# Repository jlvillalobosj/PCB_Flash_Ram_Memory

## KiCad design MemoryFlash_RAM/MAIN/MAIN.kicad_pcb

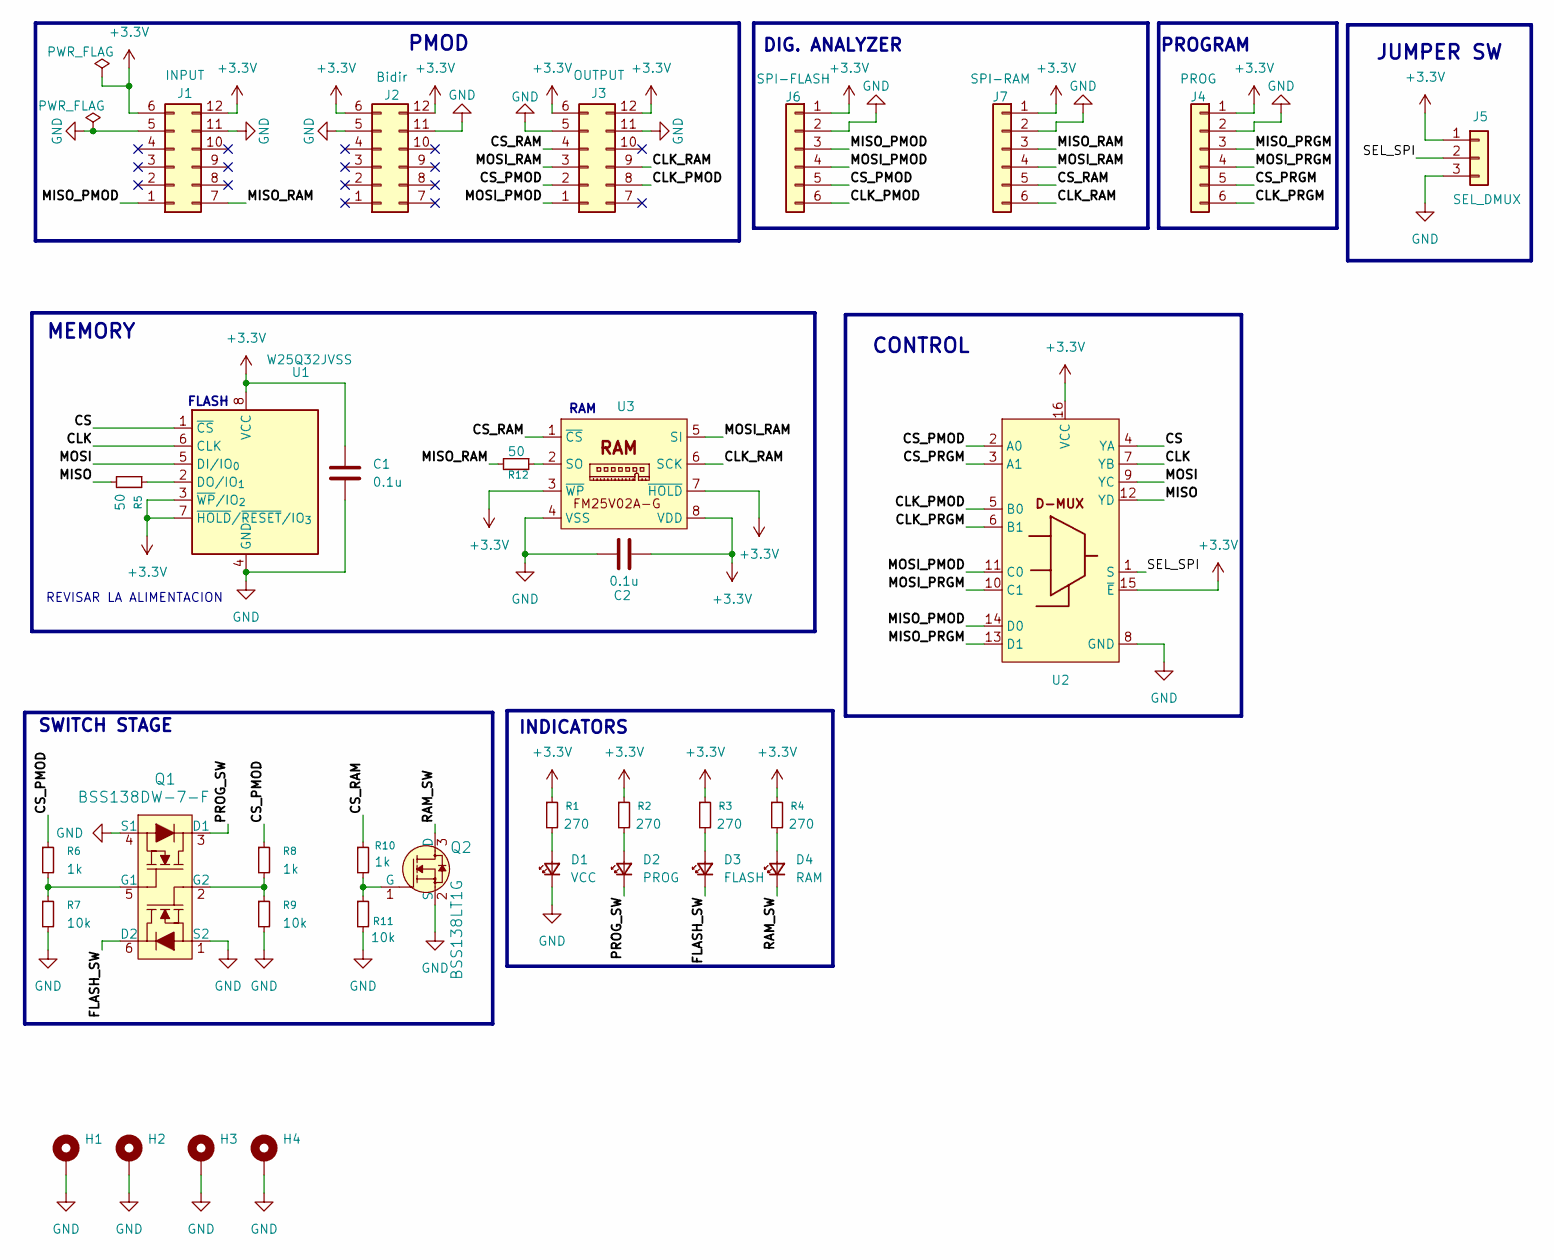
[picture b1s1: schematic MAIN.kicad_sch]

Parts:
C1, C2: 0.1u; C_0805_2012Metric
D1: VCC; LED_2010_5025Metric
D2: PROG; LED_2010_5025Metric
D3: FLASH; LED_2010_5025Metric
D4: RAM; LED_2010_5025Metric
H1, H2, H3, H4: MountingHole_Pad; MountingHole_3.2mm_M3_DIN965_Pad
J1: INPUT; PinHeader_2x06_P2.54mm_Horizontal
J2: Bidir; PinHeader_2x06_P2.54mm_Horizontal
J3: OUTPUT; PinHeader_2x06_P2.54mm_Horizontal
J4: PROG; PinHeader_1x06_P2.54mm_Vertical
J5: SEL_DMUX; PinHeader_1x03_P2.54mm_Vertical
J6: SPI-FLASH; PinHeader_1x06_P2.54mm_Vertical
J7: SPI-RAM; PinHeader_1x06_P2.54mm_Vertical
Q1: BSS138DW-7-F; SOT-363_SC-70-6; MPN BSS138DW-7-F; Digi-Key_PN BSS138DW-FDICT-ND
Q2: BSS138LT1G; SOT-23; MPN BSS138; Digi-Key_PN BSS138CT-ND
R1, R2, R3, R4: 270; R_0805_2012Metric
R5, R12: 50; R_0805_2012Metric
R6, R8, R10: 1k; R_0805_2012Metric
R7, R9, R11: 10k; R_0805_2012Metric
U1: W25Q32JVSS; SOIC-8_5.3x5.3mm_P1.27mm
U2: SSOP-16_3.9x4.9mm_P0.635mm
U3: SO-8_3.9x4.9mm_P1.27mm

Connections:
+3.3V: C1.1, C2.1, J1.6, J1.12, J2.6, J2.12, J3.6, J3.12, J4.1, J5.1, J6.1, J7.1, R1.1, R2.1, R3.1, R4.1, U1.3 (~WP/IO_{2}), U1.7 (~HOLD/~RESET/IO_{3}), U1.8 (VCC), U2.15 (~E), U2.16 (VCC), U3.3 (~WP), U3.7 (~HOLD), U3.8 (VDD)
/CLK: U1.6 (CLK), U2.7 (YB)
/CLK_PMOD: J3.8, J6.6, U2.5 (B0)
/CLK_PRGM: J4.6, U2.6 (B1)
/CLK_RAM: J3.9, J7.6, U3.6 (SCK)
/CS: U1.1 (~CS), U2.4 (YA)
/CS_PMOD: J3.2, J6.5, R6.1, R8.1, U2.2 (A0)
/CS_PRGM: J4.5, U2.3 (A1)
/CS_RAM: J3.4, J7.5, R10.1, U3.1 (~CS)
/FLASH_SW: D3.1 (K), Q1.6 (D2)
/MISO: R5.2, U2.12 (YD)
/MISO_PMOD: J1.1, J6.3, U2.14 (D0)
/MISO_PRGM: J4.3, U2.13 (D1)
/MISO_RAM: J1.7, J7.3, R12.2
/MOSI: U1.5 (DI/IO_{0}), U2.9 (YC)
/MOSI_PMOD: J3.1, J6.4, U2.11 (C0)
/MOSI_PRGM: J4.4, U2.10 (C1)
/MOSI_RAM: J3.3, J7.4, U3.5 (SI)
/PROG_SW: D2.1 (K), Q1.3 (D1)
/RAM_SW: D4.1 (K), Q2.3 (D)
/SEL_SPI: J5.2, U2.1 (S)
GND: C1.2, C2.2, D1.1 (K), H1.1, H2.1, H3.1, H4.1, J1.5, J1.11, J2.5, J2.11, J3.5, J3.11, J4.2, J5.3, J6.2, J7.2, Q1.1 (S2), Q1.4 (S1), Q2.2 (S), R7.2, R9.2, R11.2, U1.4 (GND), U2.8 (GND), U3.4 (VSS)
unnamed: D1.2 (A), R1.2
unnamed: D2.2 (A), R2.2
unnamed: D3.2 (A), R3.2
unnamed: D4.2 (A), R4.2
unnamed: Q1.5 (G1), R6.2, R7.1
unnamed: Q1.2 (G2), R8.2, R9.1
unnamed: Q2.1 (G), R10.2, R11.1
unnamed: R5.1, U1.2 (DO/IO_{1})
unnamed: R12.1, U3.2 (SO)

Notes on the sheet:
REVISAR LA ALIMENTACION
JUMPER SW
FLASH
PMOD
INDICATORS
SWITCH STAGE
MEMORY
DIG. ANALYZER
PROGRAM
CONTROL
RAM

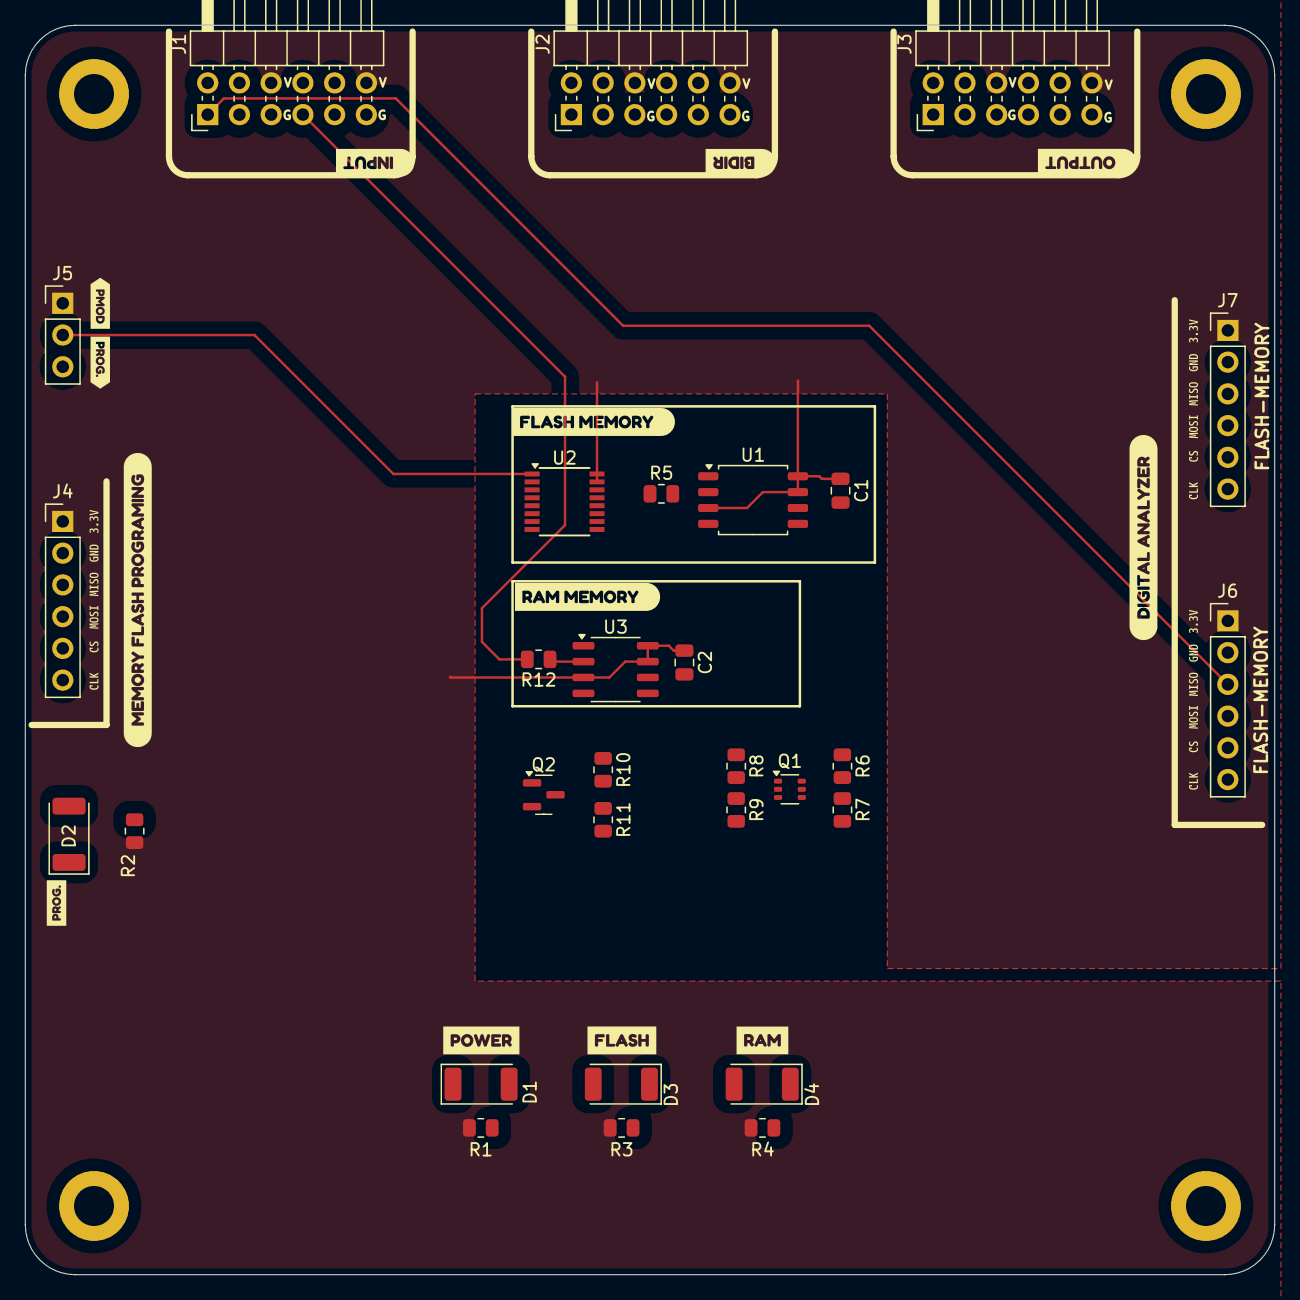
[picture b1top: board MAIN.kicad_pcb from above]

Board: 2 copper layers, 100.0 x 100.0 mm, 65 parts (0 on the bottom side), 31 nets.

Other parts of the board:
kibuzzard-6AAEAE00: G***; kibuzzard-6AAEAE00
kibuzzard-6AAEB7D3: G***; kibuzzard-6AAEB7D3
kibuzzard-6AAEB82B: G***; kibuzzard-6AAEB82B
kibuzzard-6AAEB831: G***; kibuzzard-6AAEB831
kibuzzard-6AAF2EDD: G***; kibuzzard-6AAF2EDD
kibuzzard-6AAF2EE9: G***; kibuzzard-6AAF2EE9
kibuzzard-6AAF2EF1: G***; kibuzzard-6AAF2EF1
kibuzzard-6AAF2F16: G***; kibuzzard-6AAF2F16
kibuzzard-6AAF36AB, kibuzzard-6AAF36AB#2, kibuzzard-6AAF36AB#3: G***; kibuzzard-6AAF36AB
kibuzzard-6AAF36BF, kibuzzard-6AAF36BF#2, kibuzzard-6AAF36BF#3: G***; kibuzzard-6AAF36BF
kibuzzard-6AAF36C8, kibuzzard-6AAF36C8#2, kibuzzard-6AAF36C8#3: G***; kibuzzard-6AAF36C8
kibuzzard-6AAF36D3, kibuzzard-6AAF36D3#2, kibuzzard-6AAF36D3#3: G***; kibuzzard-6AAF36D3
kibuzzard-6AAF36DA, kibuzzard-6AAF36DA#2, kibuzzard-6AAF36DA#3: G***; kibuzzard-6AAF36DA
kibuzzard-6AAF36E0, kibuzzard-6AAF36E0#2, kibuzzard-6AAF36E0#3: G***; kibuzzard-6AAF36E0
kibuzzard-6AAF347E: G***; kibuzzard-6AAF347E
kibuzzard-6AAF3046: G***; kibuzzard-6AAF3046
kibuzzard-6AAF3053: G***; kibuzzard-6AAF3053
kibuzzard-6AAF3222: G***; kibuzzard-6AAF3222
kibuzzard-6AAF3233: G***; kibuzzard-6AAF3233
